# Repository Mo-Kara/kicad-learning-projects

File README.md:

# KiCad Learning Projects

Practice boards I recreated in KiCad while learning schematic capture, footprints, PCB layout and fabrication output. **These are learning projects: the designs were reproduced from public tutorials and open designs, not original work.** The goal was to practise the workflow and to understand each circuit, not to claim the designs.

## Projects

### Tiny solar supply (`tiny-solar-supply`)
Solar-powered 3.3 V boost converter built around the AP3015 (output set by the 1 MΩ / 604 kΩ feedback divider), with a 2N7002 switch, SS14 Schottky diodes and SMD parts. I reviewed the layout and noted improvements for a Rev B (switching loop, feedback routing, ground plane, output switch-off).

### Breadboard power supply (`breadboard-power-supply`)
LM317 adjustable supply with 3.3 V / 5 V header outputs, power LED, slide switch and screw terminals. Includes Gerber files.

### Bridge rectifier (`bridge-rectifier`)
Four 1N4007 diodes, a 1000 µF smoothing capacitor and a 10 kΩ bleeder resistor and an LED indicator (2.2 kΩ) on a through-hole board with screw terminals.

### LED torch (`led-torch`)
CR2032 coin-cell LED light with push button and series resistor. Includes Gerber files.

### Work in progress
- `arduino-nano-board`: custom Arduino Nano footprint practice (no complete board yet).
- `mcu-datalogger`: early project files for an MCU data logger (not finished).

## Notes
- Made with KiCad 9. Open the `.kicad_pro` file in each folder.
- Custom symbol and footprint libraries were downloaded separately and are not included, so KiCad may report missing libraries on first open.
- Source links for the original designs: _to be added per project_.

## Author
Mohanad Al-Karajeh, Systems Engineering student, Graz.

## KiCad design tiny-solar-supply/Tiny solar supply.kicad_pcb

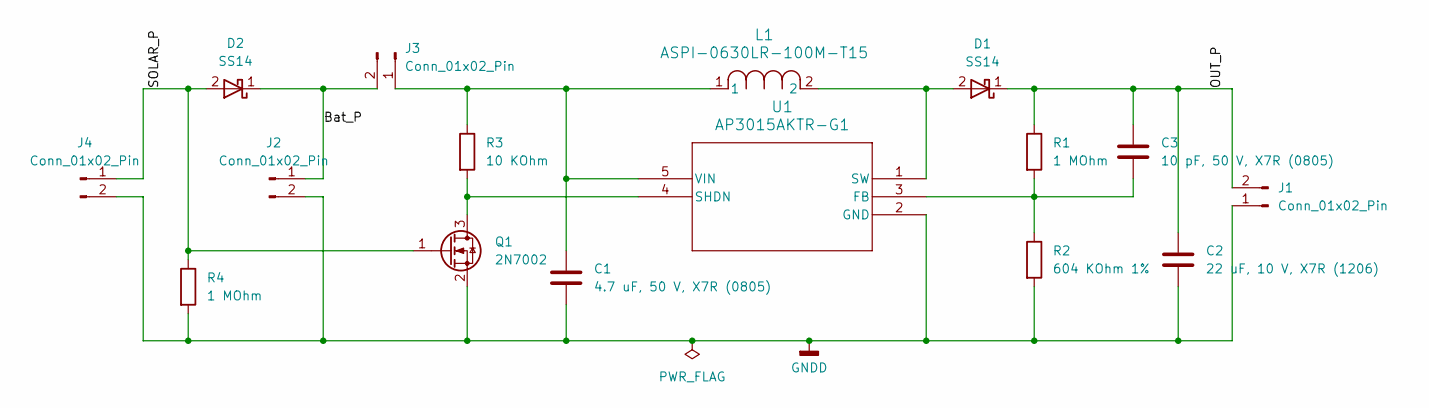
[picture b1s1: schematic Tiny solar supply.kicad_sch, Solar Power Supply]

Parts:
C1: 4.7 uF, 50 V, X7R (0805); C_0805_2012Metric
C2: 22 uF, 10 V, X7R (1206); C_1206_3216Metric
C3: 10 pF, 50 V, X7R (0805); C_0805_2012Metric
D1, D2: SS14; D_SMA
J1, J2, J3: Conn_01x02_Pin; PinHeader_1x02_P2.54mm_Vertical
J4: Conn_01x02_Pin; PinHeader_1x02_P2.54mm_Horizontal
L1: ASPI-0630LR-100M-T15; IND_ASPI-0630LR_ABR-L
Q1: 2N7002; SOT-23
R1, R4: 1 MOhm; R_0805_2012Metric
R2: 604 KOhm 1%; R_0805_2012Metric
R3: 10 KOhm; R_0805_2012Metric
U1: AP3015AKTR-G1; AP3015AKTR_G1

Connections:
/Bat_P: D2.1 (K), J2.1, J3.2
/OUT_P: C2.1, C3.1, D1.1 (K), J1.2, R1.1
/SOLAR_P: D2.2 (A), J4.1, Q1.1 (G), R4.1
GNDD: C1.2, C2.2, J1.1, J2.2, J4.2, Q1.2 (S), R2.2, R4.2, U1.2 (GND)
unnamed: D1.2 (A), L1.2, U1.1 (SW)
unnamed: C1.1, J3.1, L1.1, R3.1, U1.5 (VIN)
unnamed: Q1.3 (D), R3.2, U1.4 (SHDN)
unnamed: C3.2, R1.2, R2.1, U1.3 (FB)

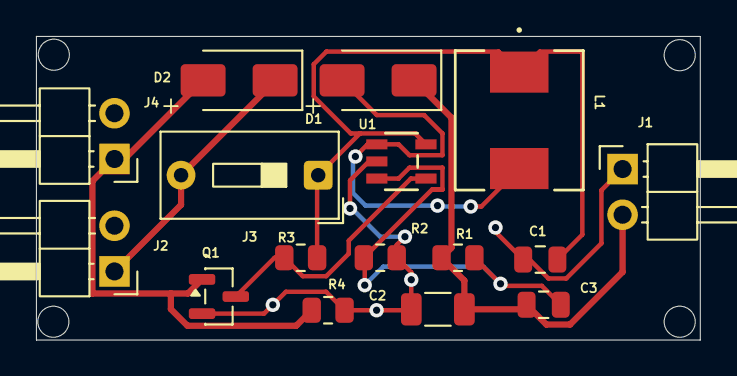
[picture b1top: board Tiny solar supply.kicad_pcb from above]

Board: 2 copper layers, 36.9 x 16.9 mm, 16 parts (0 on the bottom side), 8 nets.

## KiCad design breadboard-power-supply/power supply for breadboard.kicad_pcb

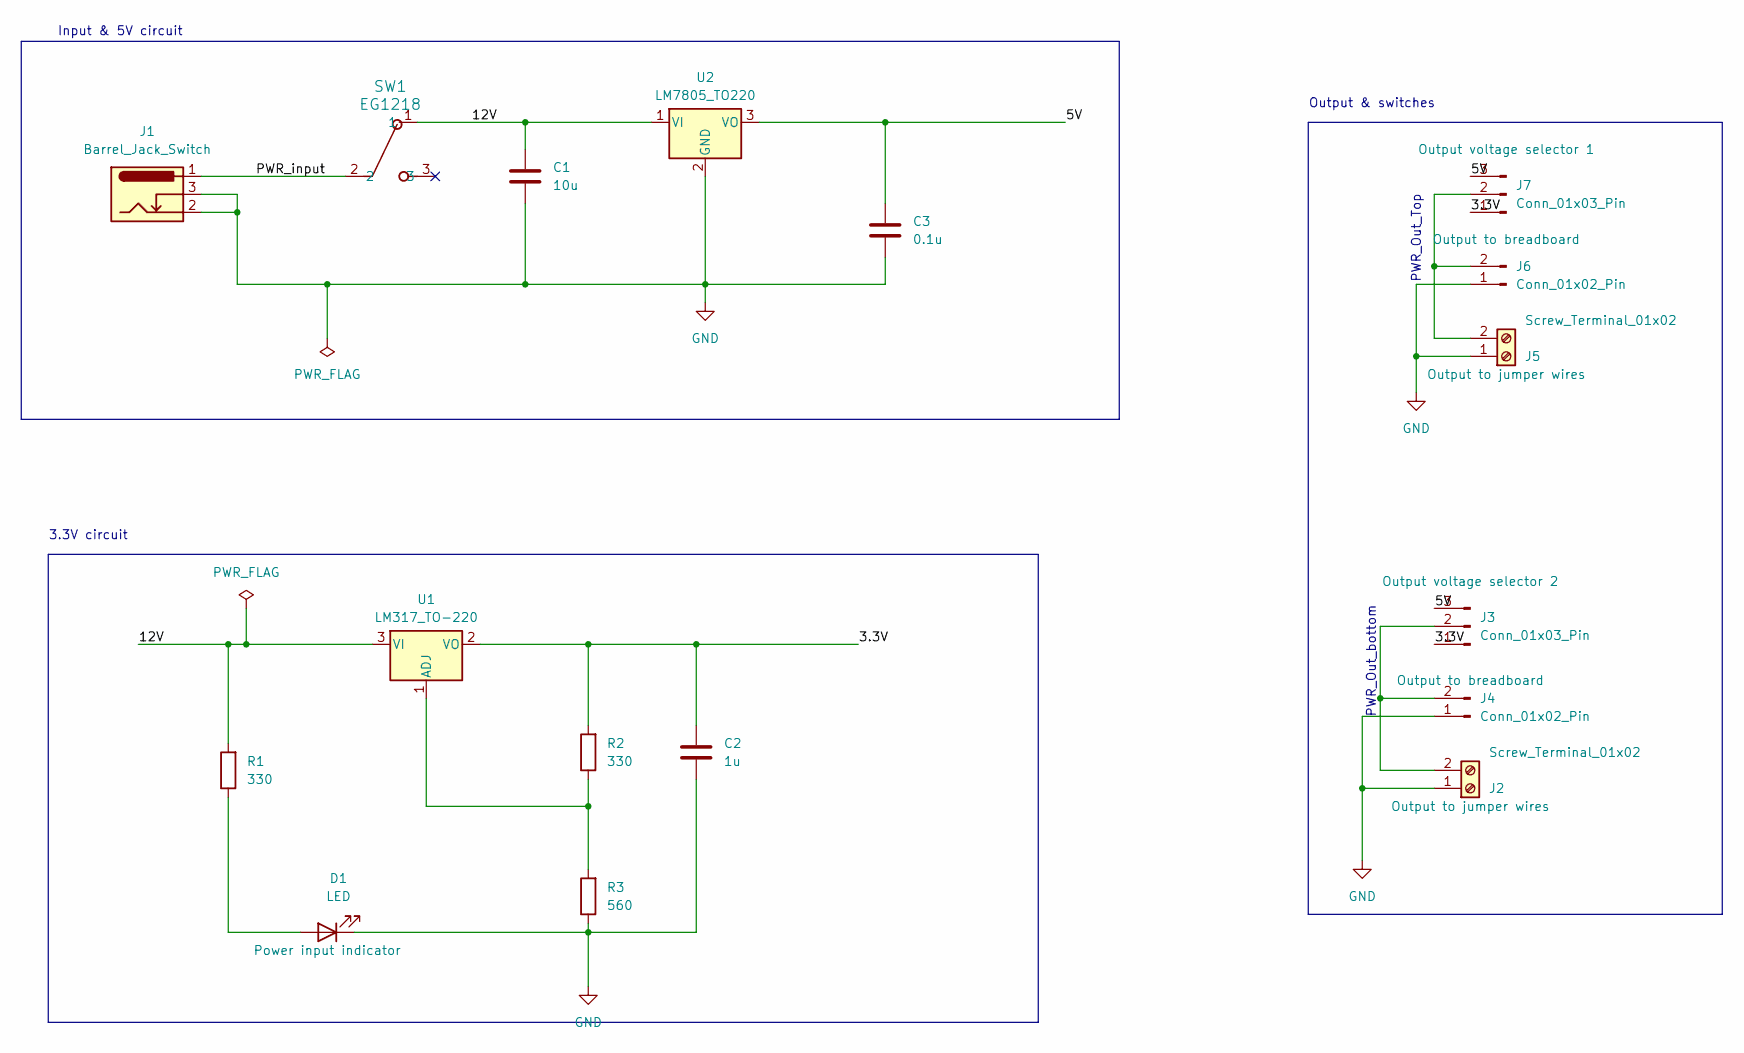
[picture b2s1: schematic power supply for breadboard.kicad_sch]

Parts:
C1: 10u; C_Disc_D3.0mm_W1.6mm_P2.50mm
C2: 1u; C_Disc_D3.0mm_W1.6mm_P2.50mm
C3: 0.1u; C_Disc_D3.0mm_W1.6mm_P2.50mm
D1: LED; LED_D5.0mm
J1: Barrel_Jack_Switch; BarrelJack_Horizontal
J2, J5: Screw_Terminal_01x02; TerminalBlock_bornier-2_P5.08mm
J3, J7: Conn_01x03_Pin; PinHeader_1x03_P2.54mm_Vertical
J4, J6: Conn_01x02_Pin; PinHeader_1x02_P2.54mm_Vertical
R1, R2: 330; R_Axial_DIN0204_L3.6mm_D1.6mm_P7.62mm_Horizontal
R3: 560; R_Axial_DIN0204_L3.6mm_D1.6mm_P7.62mm_Horizontal
SW1: EG1218; Switch_Slide_11.6x4mm_EG1218
U1: LM317_TO-220; TO-220-3_Vertical
U2: LM7805_TO220; TO-220-3_Vertical

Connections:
/3.3V: C2.1, J3.1, J7.1, R2.2, U1.2 (VO)
/5V: C3.1, J3.3, J7.3, U2.3 (VO)
/12V: C1.1, R1.2, SW1.1, U1.3 (VI), U2.1 (VI)
/PWR_input: J1.1, SW1.2
GND: C1.2, C2.2, C3.2, D1.1 (K), J1.2, J1.3, J2.1, J4.1, J5.1, J6.1, R3.1, U2.2 (GND)
unnamed: D1.2 (A), R1.1
unnamed: J2.2, J3.2, J4.2
unnamed: J5.2, J6.2, J7.2
unnamed: R2.1, R3.2, U1.1 (ADJ)

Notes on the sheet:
3.3V circuit
PWR_Out_Top
Output & switches
Input & 5V circuit
PWR_Out_bottom

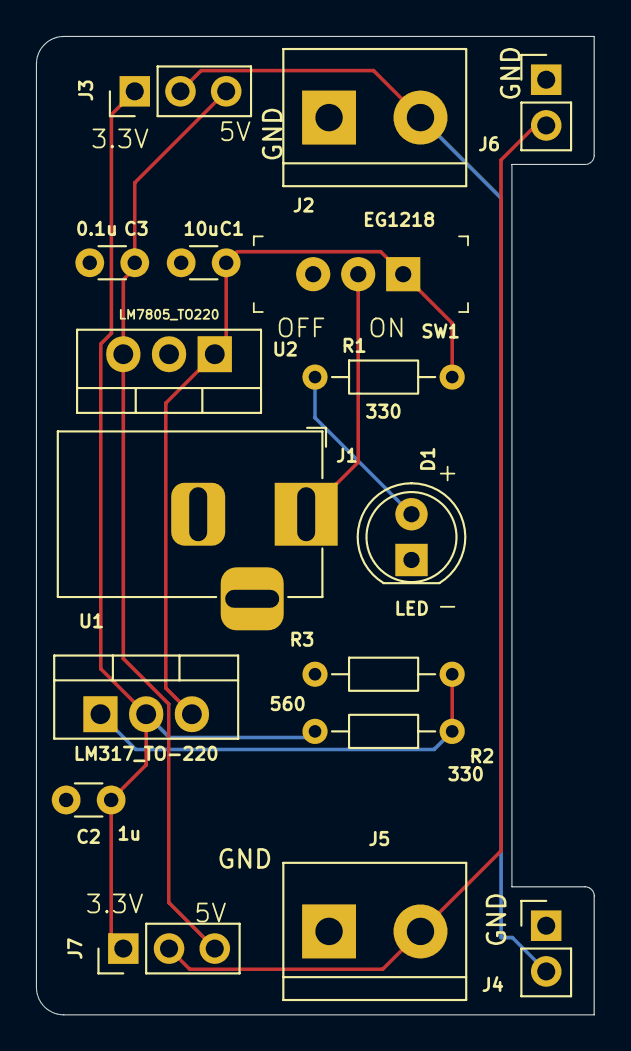
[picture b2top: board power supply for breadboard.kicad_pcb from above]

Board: 2 copper layers, 31.0 x 54.4 mm, 17 parts (0 on the bottom side), 9 nets.

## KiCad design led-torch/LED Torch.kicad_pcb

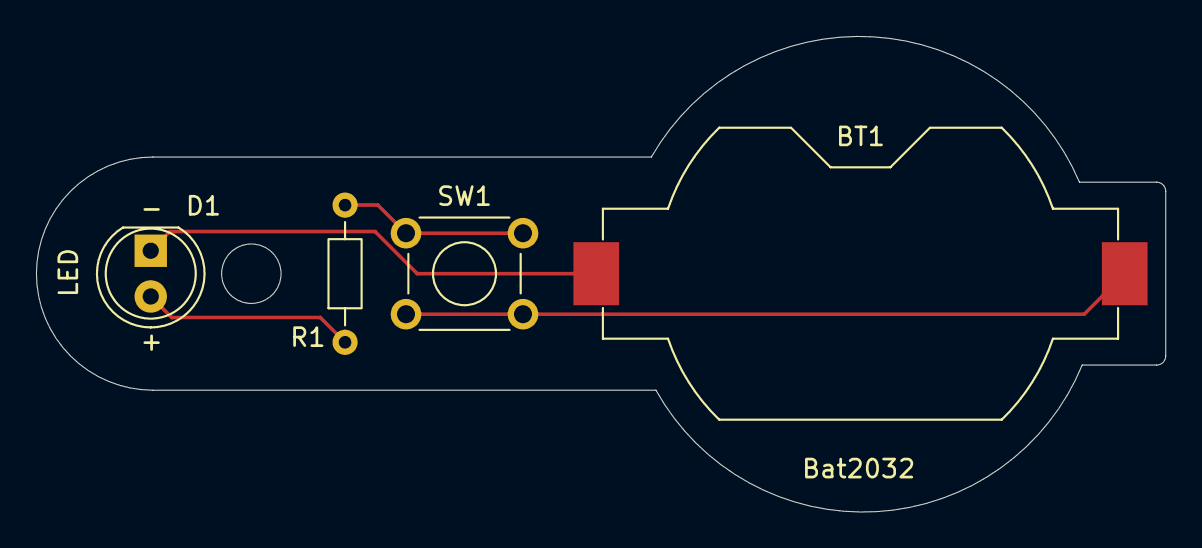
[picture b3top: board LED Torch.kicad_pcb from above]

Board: 2 copper layers, 62.7 x 26.4 mm, 4 parts (0 on the bottom side), 4 nets.

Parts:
BT1: Bat2032; BatteryHolder_Keystone_1058_1x2032
D1: LED; LED_D5.0mm
R1: R; R_Axial_DIN0204_L3.6mm_D1.6mm_P7.62mm_Horizontal
SW1: SW_DPDT_x2; SW_TH_Tactile_Omron_B3F-100x

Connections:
/LED_anode: D1.2 (A), R1.1
/bat_pos: BT1.1 (+), SW1.2 (B)
unnamed: BT1.2 (-), D1.1 (K)
unnamed: R1.2, SW1.1 (A)

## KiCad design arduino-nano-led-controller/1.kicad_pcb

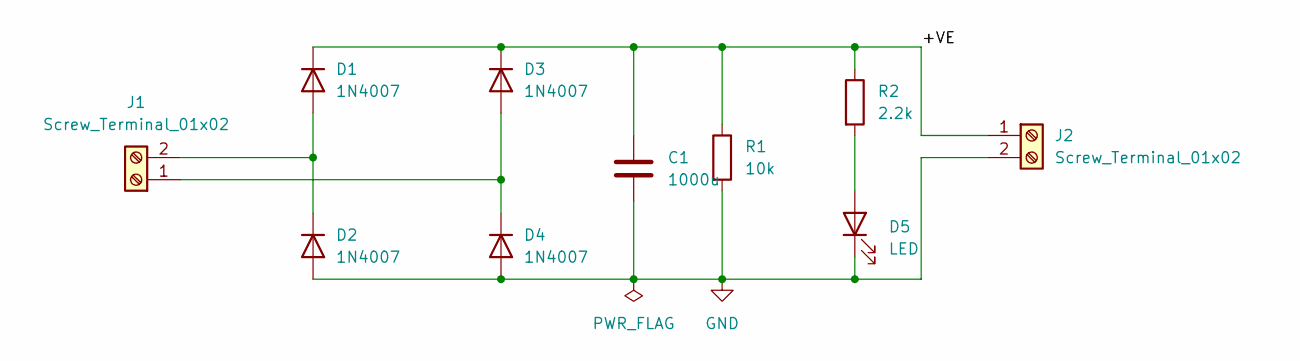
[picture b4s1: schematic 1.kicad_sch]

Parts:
C1: 1000u; CP_Radial_D8.0mm_P3.80mm
D1, D2, D3, D4: 1N4007; D_DO-41_SOD81_P10.16mm_Horizontal
D5: LED; LED_D5.0mm
J1, J2: Screw_Terminal_01x02; TerminalBlock_MaiXu_MX126-5.0-02P_1x02_P5.00mm
R1: 10k; R_Axial_DIN0207_L6.3mm_D2.5mm_P7.62mm_Horizontal
R2: 2.2k; R_Axial_DIN0207_L6.3mm_D2.5mm_P7.62mm_Horizontal

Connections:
/+VE: C1.1, D1.1 (K), D3.1 (K), J2.1, R1.1, R2.1
GND: C1.2, D2.2 (A), D4.2 (A), D5.1 (K), J2.2, R1.2
unnamed: D1.2 (A), D2.1 (K), J1.2
unnamed: D3.2 (A), D4.1 (K), J1.1
unnamed: D5.2 (A), R2.2

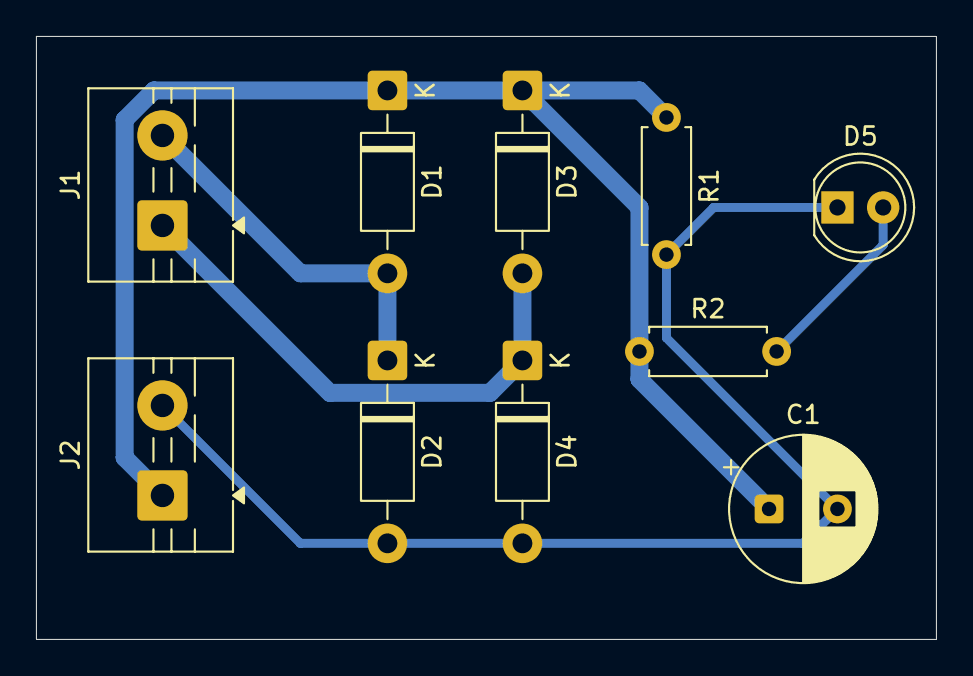
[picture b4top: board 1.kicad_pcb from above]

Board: 2 copper layers, 50.0 x 33.5 mm, 10 parts (0 on the bottom side), 5 nets.
